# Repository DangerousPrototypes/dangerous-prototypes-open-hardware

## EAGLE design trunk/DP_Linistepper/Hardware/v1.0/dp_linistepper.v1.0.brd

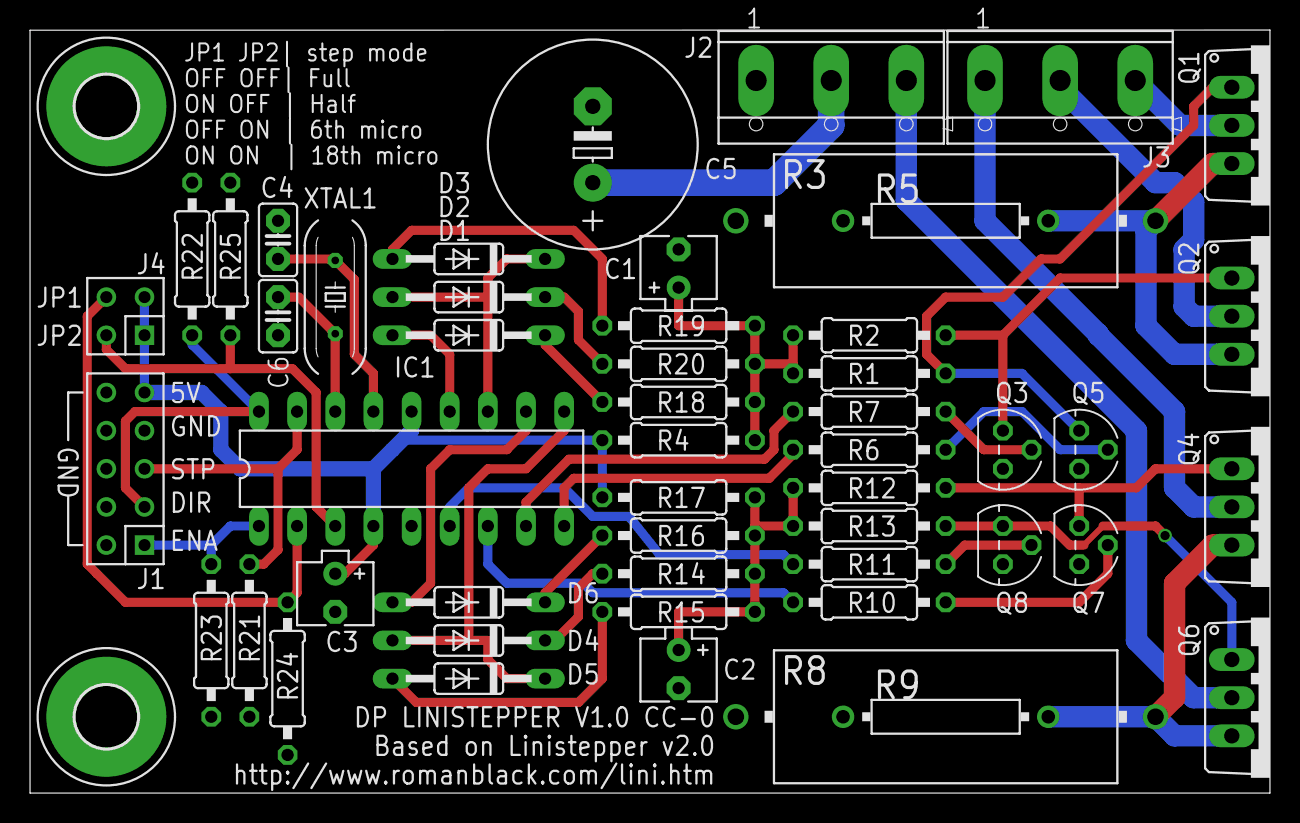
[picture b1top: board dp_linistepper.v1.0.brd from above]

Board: 2 copper layers, 82.5 x 50.8 mm, 55 parts (1 on the bottom side), 40 nets.

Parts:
C1, C2: 2.2uF 35V; ETR1
C3: 10uF 25V; ETR1
C4, C6: 22pF; C0.1PTH
C5: E5-13
D1, D2, D3, D4, D5, D6: 1N4148; DO35-10
H1, H2: MOUNT-PAD-ROUND4.1; 4,1-PAD
IC1: PIC16F628P; DIL18
J1: CON_HEADER_2X05-PTH; M2X5
J2, J3: CON_TERMINAL_BLOCK_03-5MM; TERMINAL_BLOCK_3P_5
J4: CON_HEADER_2X02-PTH; M2X2
Q1, Q2, Q4, Q6: TIP122; TO220AV
Q3, Q5, Q7, Q8: BC337; TO92
R1, R2, R12, R13: 120R; RTH025W
R3, R8: 1R 5W; HPS923
R4, R17: 470R; RTH025W
R5, R9: HPS63
R6, R7, R10, R11, R21, R22, R23, R24, R25: 3.3K; RTH025W
R14, R20: 680R; RTH025W
R15, R19: 220R; RTH025W
R16, R18: 150R; RTH025W
U$1: FRAME_DINA4_L; DP_LOGO
U$2: DP_LOGO_ART_1X1
XTAL1: 16Mhz; HC-49U-PTH

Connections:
+5V: C3.+, IC1.4, IC1.14, J1.9, J4.1, J4.3, R4.2, R17.2
A1: J3.3, Q1.2
A2: J3.2, Q2.2
B1: J3.1, Q4.2
B2: J2.3, Q6.2
DIR: IC1.18, J1.3, R22.2
ENA: IC1.1, J1.1, R23.2
GND: C1.-, C2.-, C3.-, C4.2, C5.-, C6.2, IC1.5, J1.2, J1.4, J1.6, J1.7, J1.8, J1.10, J2.1, Q3.1, Q5.1, Q7.1, Q8.1, R3.1, R5.1, R8.1, R9.1, R21.1, R22.1, R23.1, R24.1, R25.1
J1: IC1.2, J4.4, R24.2
J2: IC1.3, J4.2, R25.2
M+: C5.+, J2.2
unnamed: C4.1, IC1.15, XTAL1.P1
unnamed: C6.1, IC1.16, XTAL1.P2
unnamed: D1.C, R18.1
unnamed: D2.C, R20.1
unnamed: D3.A, R19.1
unnamed: C1.+, R1.1, R2.1, R4.1, R18.2, R19.2, R20.2
unnamed: D2.A, D3.C, IC1.12
unnamed: D1.A, IC1.13
unnamed: Q1.1, Q5.3, R1.2
unnamed: Q1.3, Q2.3, R3.2, R5.2
unnamed: Q2.1, Q3.3, R2.2
unnamed: Q5.2, R6.2
unnamed: Q3.2, R7.2
unnamed: IC1.9, R6.1
unnamed: IC1.8, R7.1
unnamed: Q4.3, Q6.3, R8.2, R9.2
unnamed: Q7.2, R10.2
unnamed: Q8.2, R11.2
unnamed: IC1.7, R10.1
unnamed: IC1.6, R11.1
unnamed: Q4.1, Q7.3, R12.2
unnamed: Q6.1, Q8.3, R13.2
unnamed: C2.+, R12.1, R13.1, R14.2, R15.2, R16.2, R17.1
unnamed: D4.C, R14.1
unnamed: D5.A, R15.1
unnamed: D6.C, R16.1
unnamed: D4.A, D5.C, IC1.10
unnamed: D6.A, IC1.11
STP: IC1.17, J1.5, R21.2

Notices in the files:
trunk/DP_Linistepper/Hardware/v1.0/dp_linistepper.v1.0.brd:
LICENSE: CC-0
